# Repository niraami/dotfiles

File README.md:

# Personal dotfiles
Dotfiles - also known as: *I'm never using linux again If I lose these files*.

## Screenshots

## Environment
- Distribution: [Arch Linux](https://www.archlinux.org/)
- Compositor: [hyprland](https://hypr.land/) (Wayland)
- Bar: [waybar](https://github.com/Alexays/Waybar)
- App launcher: [ulauncher](https://ulauncher.io/)
- Notification daemon: [swaync](https://github.com/ErikReider/SwayNotificationCenter)
- Wallpaper daemon: [awww](https://codeberg.org/LGFae/awww)
- Idle daemon: [hypridle](https://github.com/hyprwm/hypridle)
- Screen lock: [hyprlock](https://github.com/hyprwm/hyprlock)
- Color scheme:
  - [colloid-gtk](https://github.com/vinceliuice/Colloid-gtk-theme) (purple dark compact)
  - [colloid-kde](https://github.com/vinceliuice/Colloid-kde) (dark + [kvantum](https://github.com/tsujan/Kvantum))
  - [papirus-icon-theme](https://github.com/PapirusDevelopmentTeam/papirus-icon-theme) (dark)
- Fonts: [Roboto](https://fonts.google.com/specimen/Roboto), [Fantasque Sans Mono](https://github.com/belluzj/fantasque-sans), [DejaVu Sans Mono](https://dejavu-fonts.github.io/) (terminal)

## Applications
- Shell: [zsh](https://www.zsh.org/)
- Terminal: [kitty](https://sw.kovidgoyal.net/kitty/index.html)
- Text editors: [vim](http://www.vim.org/), [vscode](https://code.visualstudio.com/)
- File managers: [ranger](https://github.com/ranger/ranger), [thunar](https://docs.xfce.org/xfce/thunar/start)
- Media player: [mpv](https://mpv.io/)
- Music: [tidal-hifi](https://github.com/Mastermindzh/tidal-hifi)
- Browsers: [brave](https://brave.com/), [firefox](https://www.mozilla.org/en-US/firefox/)
- Screen capture:
  - [hyprshot](https://github.com/Gustash/Hyprshot)
  - [wf-recorder](https://github.com/ammen99/wf-recorder)
  - wrapped by a custom script ([hypr_capture.py](user/config/hypr/scripts/hypr_capture.py))
- AUR helper: [yay](https://github.com/Jguer/yay)

# Dotfiles manager
To manage both my user and system level dotfiles, I use [Dotdrop by deadc0de6](https://github.com/deadc0de6/dotdrop).

To install these dotfiles, use the following commands from within the root of the repo.  
For more information, consult the excellent [documentation](https://dotdrop.readthedocs.io/en/latest/usage/#install-dotfiles).
```bash
git submodule update --init --recursive

dotdrop --cfg="config-user.yml" install
sudo dotdrop --cfg="config-system.yml" install
```

To install dotdrop, either use the submodule in this repo, and then use `dotdrop.sh`.
```bash
python3 -m pip install --user -r dotdrop/requirements.txt
./dotdrop/bootstrap.sh

# Use dotdrop
./dotdrop.sh --cfg="config-user.yml" compare
```

Or you could install the [AUR dotdrop package](https://aur.archlinux.org/packages/dotdrop), and just use `dotdrop` like in the examples above.

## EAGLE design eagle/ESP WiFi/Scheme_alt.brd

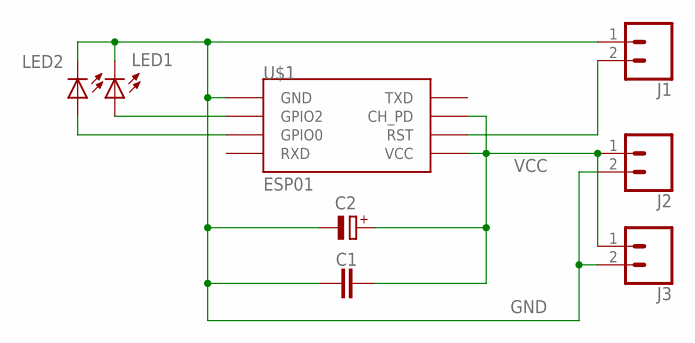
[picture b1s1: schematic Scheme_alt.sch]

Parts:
C1: C-EU025-024X044; C025-024X044
C2: CPOL-EUE5-10.5; E5-10,5
J1, J2, J3: CONN_02; 1X02
LED1, LED2: LED3MM
U$1: ESP01

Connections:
GND: C1.2, C2.-, J1.1, J2.2, J3.2, LED1.K (C), LED2.K (C), U$1.GND
unnamed: LED1.A, U$1.GPIO2
unnamed: LED2.A, U$1.GPIO0
unnamed: J1.2, U$1.RST
VCC: C1.1, C2.+, J2.1, J3.1, U$1.CH_PD, U$1.VCC

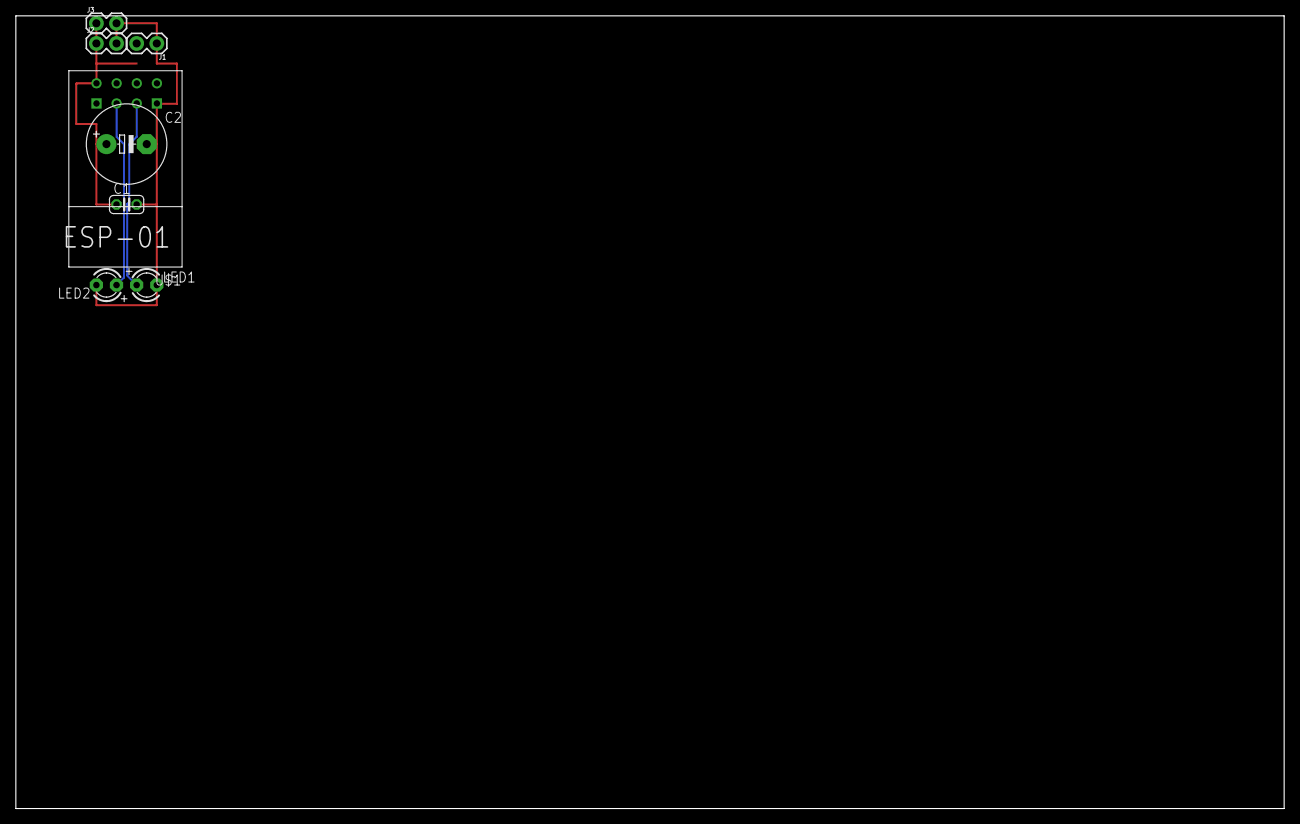
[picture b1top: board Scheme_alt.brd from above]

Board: 2 copper layers, 160.0 x 100.0 mm, 8 parts (0 on the bottom side), 5 nets.

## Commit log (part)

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2017-12-19 Fix to backlight script for HP
2017-12-19 Changed Chrome as default tab
2017-12-20 Changed coredump storage to none, after finding a 2.2GB file on root partition
2018-01-11 Random fixes and sync with rin
2018-01-12 Complete rewamp - new setup script
2018-01-12 Removed all symlinks from git - still need a gitignore implementation
2018-01-12 Fix 'if' -> 'elif' after #4d190c9
2018-01-12 Removing obsolete items
2018-01-14 Rough support for replacing directories (if such dir doesn't already exist) Also support for private files in .PRIVATE
2018-01-14 Support for Global inside .PRIVATE
2018-01-14 Attemp to fix AllowNoPassword - no luck
2018-01-14 Add all links to local exclude file
2018-01-14 Updated .PRIVATE
2018-01-14 Also remove the ignore file generated by 'setup.sh'
2018-01-15 Switch to proper contains function for the if's
    File links are now physical
2018-01-15 temporarily disabling DEPS
2018-01-15 Proper Ethminer setup (Systemd Service)
2018-01-30 Fixed Git submodules initializing before entering the correct folder
2018-02-23 New wallpaper for Rin - along with new Grub2 theme
2018-02-23 Tweaks during reinstall - new perms
2018-02-23 Moved Rin's httpd to Variant
2018-02-23 Changed boot wallpaper format to PNG
2018-02-23 Also removed startx... fixed
2018-03-09 Feh alias
2018-03-09 Added new packages + moved some
2018-03-14 Classic borders - for touch (kinda) touch screen support Removed battery watchdog, this notebook doesn't really need it. Proper boot script launch that doesn't block.
2018-03-14 Depreceated scripts
2018-03-14 Modified csgo config
2018-03-24 Switched to variable for browser - for faster changes if needed
2018-11-16 Added package files for quicker install
2020-12-02 Fixed a few issues with ZSH themes
    It's not an ideal fix, but It'll work and it's probably the cleanest solution.
    - context: as oh-my-zsh is a submodule, the themes/ weren't persistent.
    So now I pull the theme from git, and link it into themes/ via Dotbot
2020-12-02 Fixes & minor modifications - changed `smart_gaps` to `inverse_outer` to get a little gap around single windows - added `udevil` to dotbot package installer & to i3 startup (devmon) - temporarily cha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
2020-12-02 Implemented notification support I've discovered that the notification center also has a `-bin` package... So I've added that and tinkered around with a few of the settings! - added deadd-notificatio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
    I've left `vsync = true` in picom config on purpose, so that it fails to launch in a VM, but will run in normal environments - crude but works for now
2020-12-03 Fixed dotbot-sudo
2020-12-03 Cleaned up old/redundant files
2020-12-04 Added autoupdate-oh-my-zsh-plugins
2020-12-07 Simplified polybars color names
    Mostly for flexibility and ease of modification
    Readability improvement for #2
2020-12-08 Minor tweaks to polybar config
2020-12-08 Added basic readme
    -- amended
2020-12-13 Cleanup & fixes
    - removed 'removemake' flag from some packages - it makes sense to keep
    the dependencies so they don't have to be downloaded again when the
    packages need an update
    - removed some unnecessary "path:" tags
    - added some core utilities to package list (ranger, w3m, rsync)
2020-12-13 Removed yay & sudo plugins from integration tests
2020-12-13 Fixed missing sudo in travis.yml
2020-12-13 I guess before_script is not a thing in arch-travis..?
    - moved commands from before_script to before_install
    - added vim command to the list as it keeps failing as well (my guess is
    16 term colors...)
    - removed python nightly version temporarily to take load off of travis
    servers while I keep retesting my setup
2020-12-13 More fixes for Travis integration
2020-12-13 Added build tag readme title
    - added build tag
    - changed sudo to true (may help with the /etc/resolv.conf failure)
    - restored `nightly` python version testing
2020-12-13 Final Travis fixes
2020-12-13 Split up Travis testing into subtasks
2020-12-13 Added spicetify theme Dribbblish (Dracula)
2020-12-14 Added startup apps, tweaked configs
    - added sycnthingtray, spotify-tray & discord (minimized) to i3 startup
    list (syncthingtray can also do .desktop, but it doesn't work well
    with i3)
    - added spotify-tray-git as a dependency
    - removed i3 output redirect from xinitrx (no real reason, mostly
    because it doesn't matter, and most people use it this way)
2020-12-14 Generic fixes for startup & spicetify
    - fixed some startup options, so all programs start correctly
    - fixed spicetify typo & commands that I forgot I used...
    - modified keepass config with useful defautls
2020-12-15 Updated oh-my-zsh
2020-12-15 Fixed some spicetify install issues w/o display
2020-12-15 Fixed typo in .travis.yml & removed custom home folder
2020-12-17 Moved DNS related config to the top
2020-12-17 Minor fixes
2020-12-20 Turned off screen blanking after 15 minutes
2020-12-20 Moved all autostart scripts to .desktop files
2021-01-20 Fixed core dump on urxvt exit
2021-01-20 General updates
2021-02-16 Added zsh syntax highlighting to oh-my-zsh & zshrc
2021-02-18 Tweaked aliases
2021-02-20 Updated themes, minor fixes
2021-02-20 Removed mailspring dependency, added vscode & lxappearance
2021-02-21 Various theme tweaks - to unify the look
2021-02-21 Ulauncher tweaks
2021-02-22 Added feh desktop entry, yt search to Ulauncher...
    added ranger alias to zshrc, added evince to dependencies & changed the
    keepassxc default settings
2021-02-23 Fixed zsh-auto-notify submodule path
2021-02-24 Added more extensions & replaced YT shortcut
2021-02-25 Added unicode extension for Ulauncher
2021-02-25 Added pop-up windows to floating exclusions
2021-02-26 Imported mpv configs
2021-02-28 Updated submodules
2021-03-05 Polybar: added a no-mode workspace module
2021-03-06 Icon & theme color sync
    Most UI elements now use my purple & dark grey color scheme
    Also switched over from material icons to font-awesome... still having
    issues with some icons refusing to render no matter what - just like
    with material icons..
2021-03-06 Polybar & Rofi: finally fixed icons..
2021-03-07 Polybar & Deadd modifications
    - changed notification center icon
    - implemented IPC hooks to change the icon (upon receiving a
    notification) - there is no way to script this with deadd yet tho
    - cleaned up the deadd config file
2021-03-09 Implemented basic functionality
2021-03-12 Fixed image preview issues in Alacritty
    Even before, there were some issues with w3m & urxvt (trying to scroll
    past the beginning or end blanked the image, when scrolling, the image
    sometimes didn't render until the window refreshed, etc), but Alacritty was
    pretty much impossible to work with - the images dissapeared about 1s
    after displaying.
2021-03-22 Minor improvements
2021-03-24 General upgrade of all submodules
2021-04-11 Small improvements & fixes
    - updated submodules
    - fixed syncthing windows floating
    - added fullscreen screenshot keybind (Control+Print)
    - added custom network script that replaces the need for per-device
    polybar configuration, and also supports multiple interfaces at once
    (shows only the default one)
2021-07-13 Fixed TERM for SSH, improved st-tray .desktop, etc
    No real notable changes, just some minor fixes
2021-07-23 Removed travis.yml
2021-12-05 Miscellaneous fixes & updates
    - fix: flameshot path name
    - add: imv image viewer as default for SVGs
    - removed Stack Overflow Ulauncher shortcut
    - removed automatic rehash from zshrc
    - update htoprc config
2021-12-05 fix: flameshot capture script typo
2021-12-05 Update Ulauncher extensions
    - removed extensions i didn't really learn to use (Spotify, Kill, Arch
    pkg, Bluetoothctl)
    - added new (probably more useful) extensions (TLDR, Weather)
2021-12-05 Removed dotbot-yay for package management
    Essentially what I've done is inpired by the LARBS project from
    LukeSmithxyz, where he also has a progs.csv file for all his prefered
    packages.
    I like it because it gives me a good format to also attach other useful
    data, like the tags and purpose.
    Explanations of tags:
2021-12-05 fix: .scripts -> scripts to follow dotbot conventions
2021-12-06 Implement etckeeper
    My `/etc` is now managed via the great etckeeper tools. I've got a
    separate 'dotfiles-etc' repository handling all those files, that is now
    just linked as a submodule into my dotfiles.
    The file structure has not changed, but many extra files are now
    tracked, and more will be as my system evolves.
    I've still got to recover the automatic setup of /etc on install, but
2021-12-06 Change compdump folder for zsh to ~/.cache/zsh
2021-12-06 Add rehash hook for ZSH via a USR1 trap
    See https://wiki.archlinux.org/title/zsh#Alternative_on-demand_rehash_using_SIGUSR1
    for more information.
    Also see my etc dotfiles, specifically /etc/pacman.d/hooks/zsh-rehash.hook
2021-12-08 add: qBittorrent config & dependency
2021-12-08 Changed main title of guide, added sources
2021-12-09 guide.md: minor fixes & formatting improvements
2021-12-10 Update submodules to latest
2021-12-10 fix: typo
2021-12-11 guide.md: add section on etckeeper
2021-12-18 guide.md: improvements + fixed package CSVs
    - cleaned up the systemd-boot page
    - fixed formatting in the CSVs so that GitHub can display them properly
2022-07-23 chore: fixes & updates (large commit)
2022-08-31 chore: remove unused apps
2022-10-15 chore: update submodules to latest
    Also fixed the Vim theme, as the original github user no longer exists
2023-05-06 Major refactor - dotdrop, wayland
    This is the culmination of dotfiles, that I've ended up with after 2
    months of tinkering with Hyprland, and Wayland in general. Most of the
    configuration files have written from scratch as I've wanted to
    completely change the theme and behaviour of my environment.
    I've also switched to a (in my opinion) superior dotfile manager,
    Dotdrop, as it allows me to interact with the dofiles from anywhere,
2023-05-08 chore: behaviour changes to various apps
2023-06-03 feature: improve reliability of custom waybar modules
2023-06-19 feature: add limit to ZFS memory usage
2023-06-19 chore: update submodules
2023-10-30 chore: update pacman config & increase parallel downloads
2023-10-30 chore: update swaync config
2023-10-30 chore: hyprland-related updates to configs
2023-10-30 feature: add night light & idle inhibit to waybar
2023-10-30 feature: add flameshot
2023-10-30 chore: rename night_light script
2023-11-01 chore: minor script and config fixes
2023-11-03 chore: restructure scripts
2024-01-06 chore: change Hyprland launch script
2024-01-06 feature: add gtklock config
    note: gtklock is now deprecated, as they haven't updated to the new
    ext-session-lock-v1 protocol... but I wanna keep the files for future
    reference anyways
    gtklock issue: https://github.com/jovanlanik/gtklock/issues/53
2024-01-06 misc: various minor script & config changes
2024-02-06 chore: cleanup blender configs
2024-02-06 feature: add monitorctl hyprland script

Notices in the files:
parts and their libraries:
SparkFun-Connectors: Licensing: Creative Commons ShareAlike 4.0 International - https://creativecommons.org/licenses/by-sa/4.0
